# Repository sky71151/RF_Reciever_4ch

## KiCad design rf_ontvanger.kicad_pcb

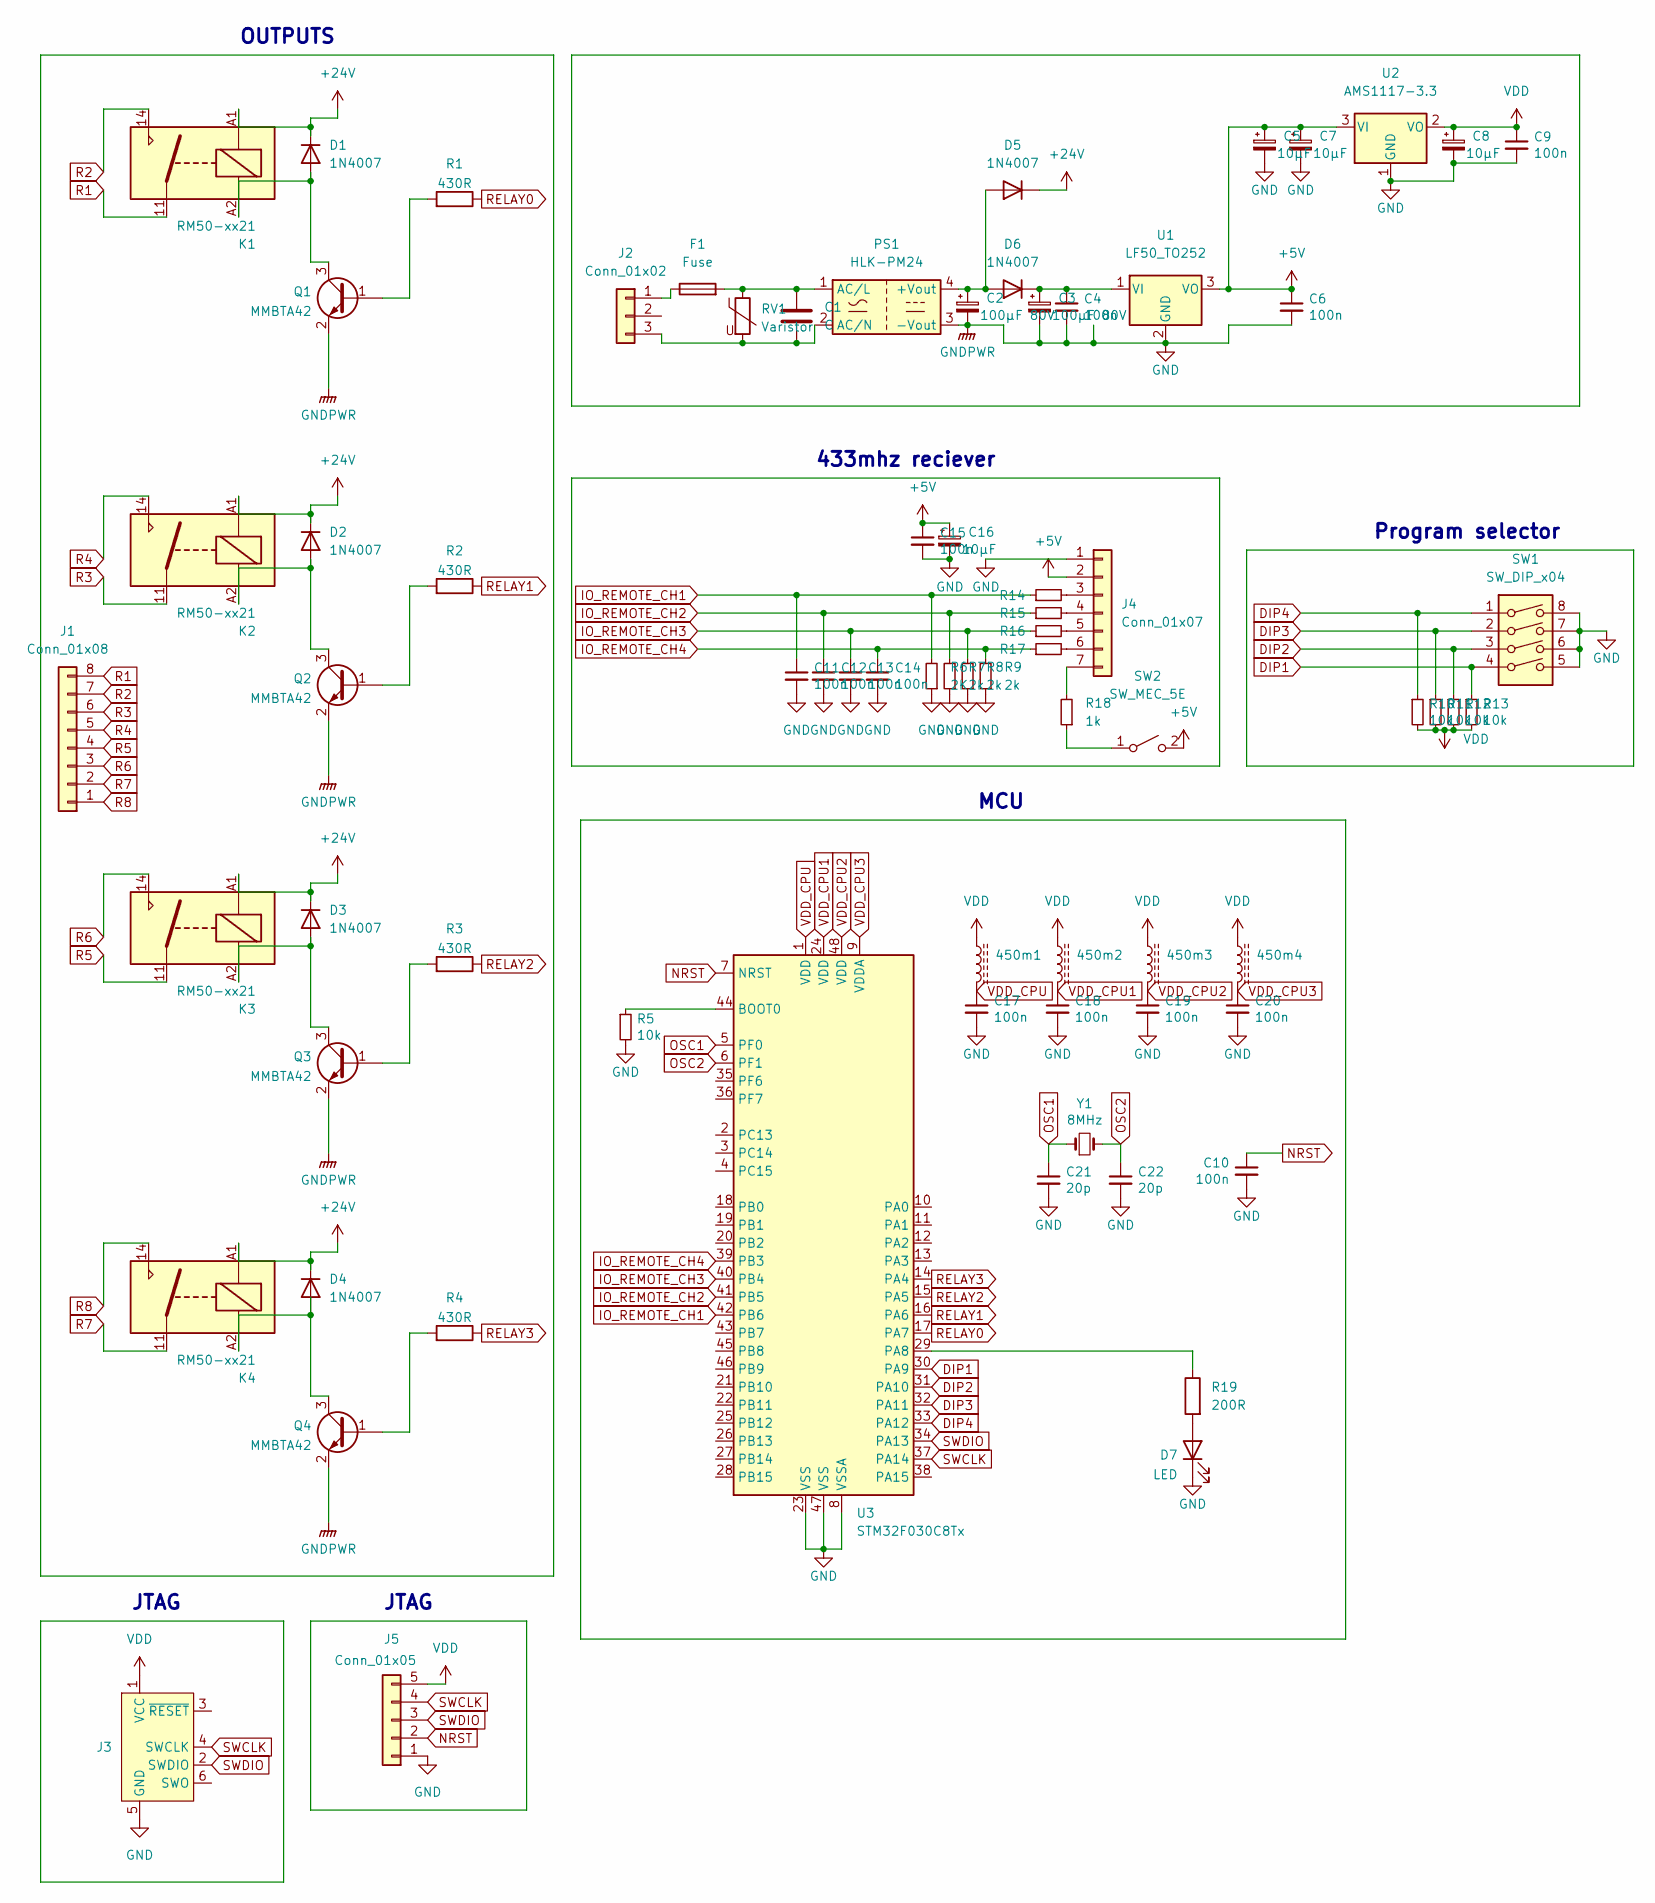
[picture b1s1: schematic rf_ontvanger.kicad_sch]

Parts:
450m1, 450m2, 450m3, 450m4: L_Ferrite; R_0603_1608Metric; LCSC C1002
C1: C; C_Rect_L16.5mm_W5.0mm_P15.00mm_MKT; LCSC C489085
C2, C3: 100µF 80V; CP_Elec_10x10; LCSC C249733
C4, C6, C9, C10, C11, C12, C13, C14, C15, C17, C18, C19, C20: 100n; C_0402_1005Metric; LCSC Part # C1525
C5, C7, C8, C16: 10µF; CP_EIA-3216-10_Kemet-I; LCSC C7171
C21, C22: 20p; C_0603_1608Metric; LCSC Part # C1648
D1, D2, D3, D4: 1N4007; D_SOD-123F; LCSC C64898
D5, D6: 1N4007; D_SOD-123F; LCSC C2892681
D7: LED; LED_0603_1608Metric; LCSC C72041
F1: Fuse; RV_Disc_D9mm_W5.7mm_P5mm; LCSC C20873
J1: Conn_01x08; TerminalBlock_Phoenix_PT-1,5-8-5.0-H_1x08_P5.00mm_Horizontal; LCSC C395863
J2: Conn_01x02; TerminalBlock_Phoenix_PT-1,5-3-5.0-H_1x03_P5.00mm_Horizontal; LCSC C484209
J3: Conn_ARM_SWD_TagConnect_TC2030; Tag-Connect_TC2030-IDC-FP_2x03_P1.27mm_Vertical
J4: Conn_01x07; PinHeader_1x07_P2.54mm_Vertical
J5: Conn_01x05; PinHeader_1x05_P2.54mm_Vertical
K1, K2, K3, K4: RM50-xx21; Relay_SPST_Finder_32.21-x300; LCSC C89311
PS1: HLK-PM24; Converter_ACDC_HiLink_HLK-PMxx
Q1, Q2, Q3, Q4: MMBTA42; SOT-23; LCSC C8512
R1, R2, R3, R4: 430R; R_0603_1608Metric; LCSC C23170
R5, R10, R11, R12, R13: 10k; R_0402_1005Metric; LCSC Part # C25744
R6: 2K; R_0402_1005Metric; LCSC C4109
R7, R8, R9: 2k; R_0402_1005Metric; LCSC C4109
R14, R15, R16, R17: 1k; R_0402_1005Metric; LCSC C11702
R18: 1k; R_0402_1005Metric; LCSC C21190
R19: 200R; R_0603_1608Metric; LCSC C8218
RV1: Varistor; RV_Disc_D12mm_W3.9mm_P7.5mm; LCSC C2839517
SW1: SW_DIP_x04; DIP-8_W8.89mm_SMDSocket_LongPads; LCSC C976366
SW2: SW_MEC_5E; SW_SPST_TL3305A; LCSC C318884
U1: LF50_TO252; TO-252-2; LCSC C58069
U2: AMS1117-3.3; SOT-223-3_TabPin2; LCSC C6186
U3: STM32F030C8Tx; LQFP-48_7x7mm_P0.5mm; LCSC C23922
Y1: 8MHz; Crystal_SMD_5032-2Pin_5.0x3.2mm; LCSC Part # C115962

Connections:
+5V: C5.1, C6.1, C7.1, C15.1, C16.1, J4.2, SW2.2 (B), U1.3 (VO), U2.3 (VI)
+24V: D1.1 (K), D2.1 (K), D3.1 (K), D4.1 (K), D5.1 (K), K1.A1, K2.A1, K3.A1, K4.A1
DIP1: R13.1, SW1.4, U3.30 (PA9)
DIP2: R12.1, SW1.3, U3.31 (PA10)
DIP3: R11.1, SW1.2, U3.32 (PA11)
DIP4: R10.1, SW1.1, U3.33 (PA12)
GND: C2.2, C3.2, C4.2, C5.2, C6.2, C7.2, C8.2, C9.2, C10.2, C11.2, C12.2, C13.2, C14.2, C15.2, C16.2, C17.2, C18.2, C19.2, C20.2, C21.2, C22.2, D7.1 (K), J3.5 (GND), J4.1, J5.1, PS1.3 (-Vout), Q1.2 (E), Q2.2 (E), Q3.2 (E), Q4.2 (E), R5.2, R6.1, R7.1, R8.1, R9.1, SW1.5, SW1.6, SW1.7, SW1.8, U1.2 (GND), U2.1 (GND), U3.8 (VSSA), U3.23 (VSS), U3.47 (VSS)
IO_REMOTE_CH1: C11.1, R6.2, R14.1, U3.42 (PB6)
IO_REMOTE_CH2: C12.1, R7.2, R15.1, U3.41 (PB5)
IO_REMOTE_CH3: C13.1, R8.2, R16.1, U3.40 (PB4)
IO_REMOTE_CH4: C14.1, R9.2, R17.1, U3.39 (PB3)
NRST: C10.1, J5.2, U3.7 (NRST)
unnamed: C1.1, F1.2, PS1.1 (AC/L), RV1.1
unnamed: C1.2, J2.3, PS1.2 (AC/N), RV1.2
unnamed: C2.1, D5.2 (A), D6.2 (A), PS1.4 (+Vout)
unnamed: C3.1, C4.1, D6.1 (K), U1.1 (VI)
unnamed: D1.2 (A), K1.A2, Q1.3 (C)
unnamed: D2.2 (A), K2.A2, Q2.3 (C)
unnamed: D3.2 (A), K3.A2, Q3.3 (C)
unnamed: D4.2 (A), K4.A2, Q4.3 (C)
unnamed: D7.2 (A), R19.2
unnamed: F1.1, J2.1
unnamed: J4.3, R14.2
unnamed: J4.4, R15.2
unnamed: J4.5, R16.2
unnamed: J4.6, R17.2
unnamed: J4.7, R18.2
unnamed: Q1.1 (B), R1.2
unnamed: Q2.1 (B), R2.2
unnamed: Q3.1 (B), R3.2
unnamed: Q4.1 (B), R4.2
unnamed: R5.1, U3.44 (BOOT0)
unnamed: R18.1, SW2.1 (A)
unnamed: R19.1, U3.29 (PA8)
OSC1: C21.1, U3.5 (PF0), Y1.1
OSC2: C22.1, U3.6 (PF1), Y1.2
R1: J1.8, K1.11
R2: J1.7, K1.14
R3: J1.6, K2.11
R4: J1.5, K2.14
R5: J1.4, K3.11
R6: J1.3, K3.14
R7: J1.2, K4.11
R8: J1.1, K4.14
RELAY0: R1.1, U3.17 (PA7)
RELAY1: R2.1, U3.16 (PA6)
RELAY2: R3.1, U3.15 (PA5)
RELAY3: R4.1, U3.14 (PA4)
SWCLK: J3.4 (SWCLK), J5.4, U3.37 (PA14)
SWDIO: J3.2 (SWDIO), J5.3, U3.34 (PA13)
VDD: 450m1.1, 450m2.1, 450m3.1, 450m4.1, C8.1, C9.1, J3.1 (VCC), J5.5, R10.2, R11.2, R12.2, R13.2, U2.2 (VO)
VDD_CPU: 450m1.2, C17.1, U3.1 (VDD)
VDD_CPU1: 450m2.2, C18.1, U3.24 (VDD)
VDD_CPU2: 450m3.2, C19.1, U3.48 (VDD)
VDD_CPU3: 450m4.2, C20.1, U3.9 (VDDA)

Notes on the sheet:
433mhz reciever
JTAG
Program selector
OUTPUTS
MCU

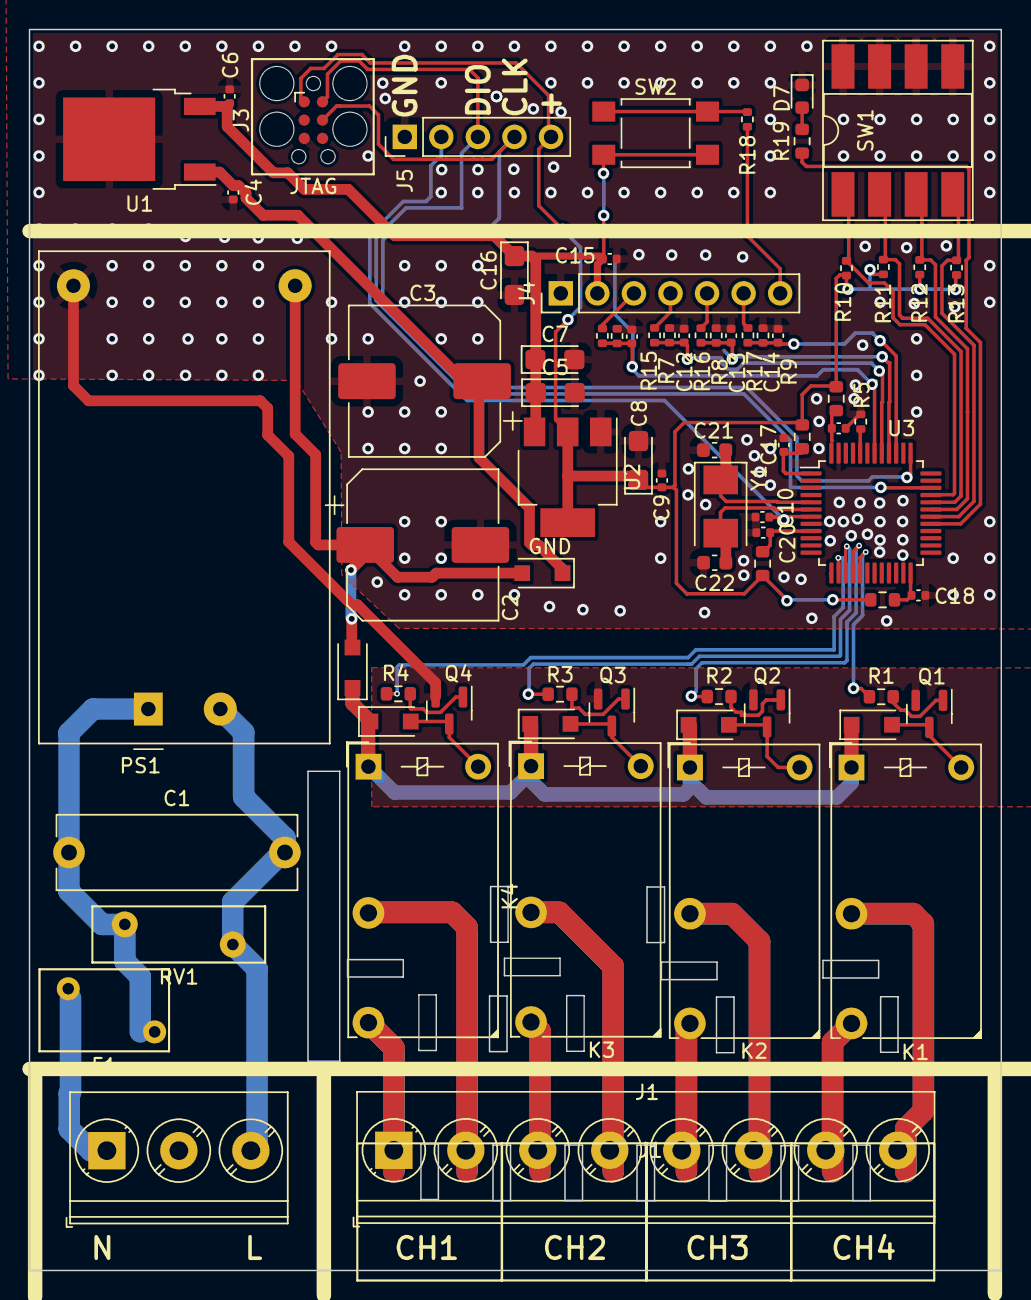
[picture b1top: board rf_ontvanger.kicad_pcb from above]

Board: 2 copper layers, 67.5 x 86.2 mm, 74 parts (0 on the bottom side), 55 nets.
